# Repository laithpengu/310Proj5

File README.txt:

CMPE 310
Cole Cavanagh & Ethan Swain
Assignment 5: KICAD

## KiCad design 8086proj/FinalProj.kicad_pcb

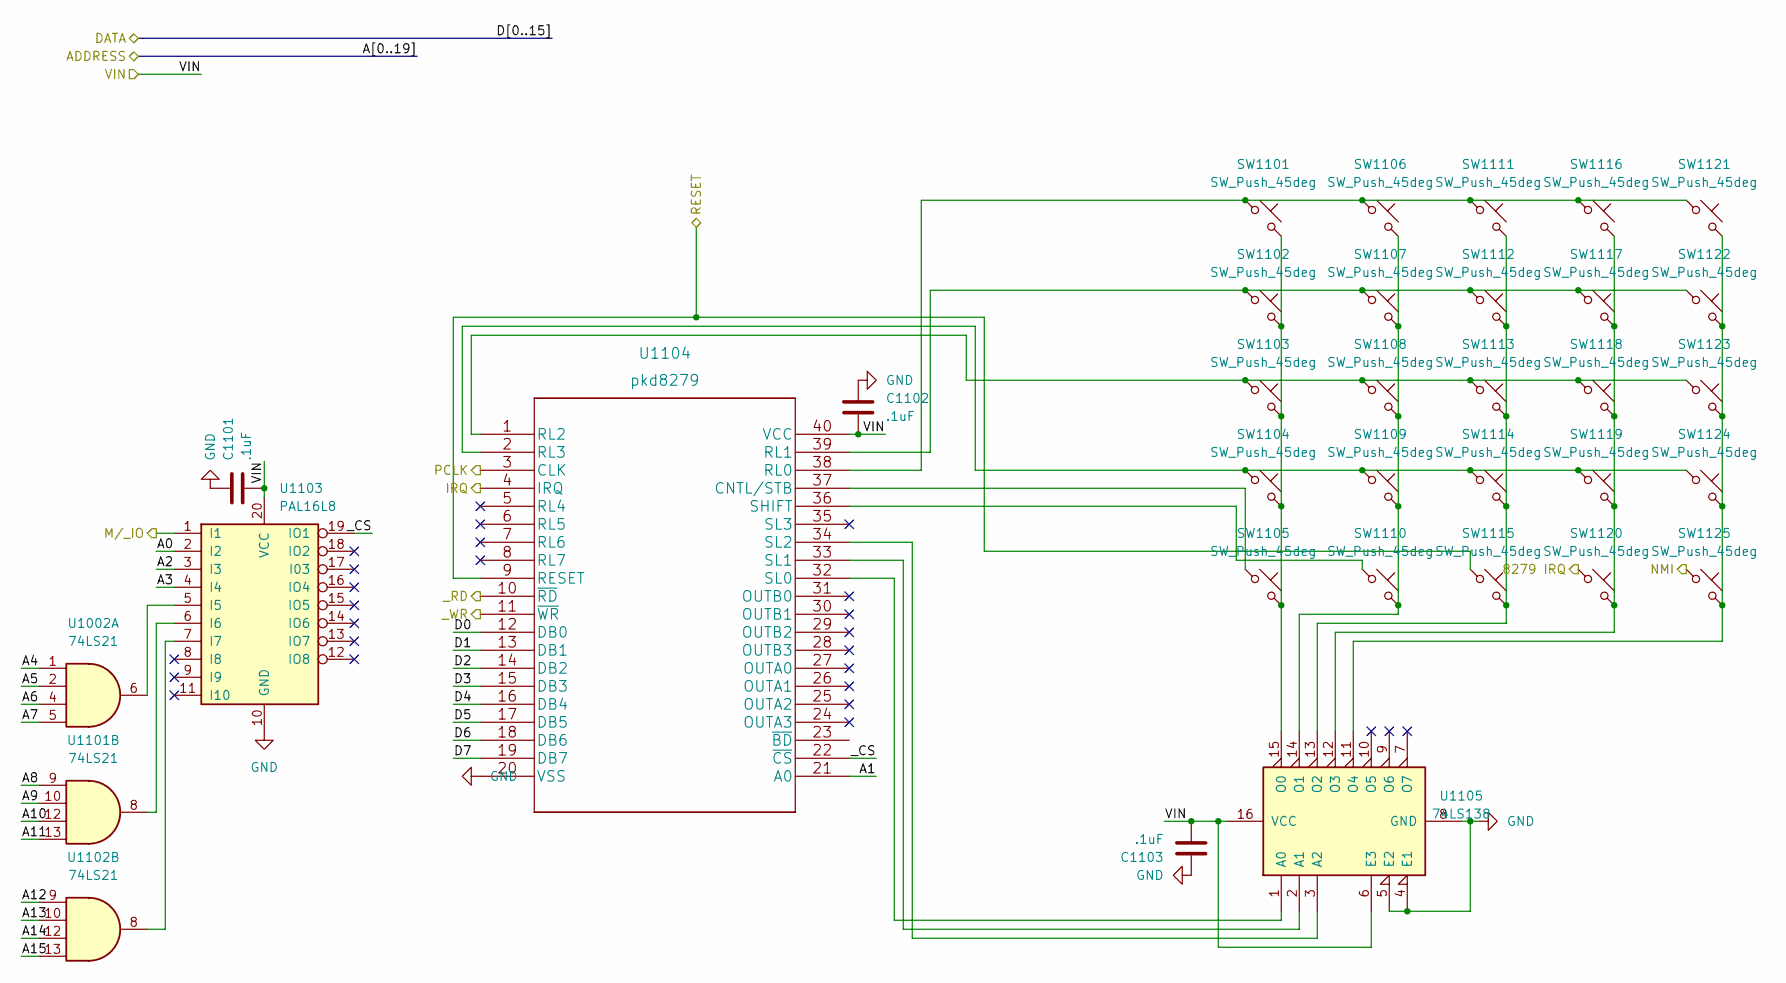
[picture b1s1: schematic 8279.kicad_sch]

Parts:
C1101, C1102, C1103: .1uF; CP_Elec_3x5.3
SW1101, SW1102, SW1103, SW1104, SW1105, SW1106, SW1107, SW1108, SW1109, SW1110, SW1111, SW1112, SW1113, SW1114, SW1115, SW1116, SW1117, SW1118, SW1119, SW1120, SW1121, SW1122, SW1123, SW1124, SW1125: SW_Push_45deg; SW_Cherry_MX_1.00u_Plate
U1002, U1101, U1102: 74LS21; DIP-14_W10.16mm
U1103: PAL16L8; DIP-20_W7.62mm
U1104: pkd8279; DIP-40_W25.4mm
U1105: 74LS138; DIP-16_W7.62mm

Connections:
/8086/INTR: U1104.4 (IRQ); also elsewhere on the board
/8086/NMI: SW1125.1; also elsewhere on the board
/8254/C2out: U1104.3 (CLK); also elsewhere on the board
/8259/8279 IRQ: SW1120.1; also elsewhere on the board
/8279/_CS: U1103.19 (IO1), U1104.22 (~CS)
/16550/A0: U1103.2 (I2); also elsewhere on the board
/16550/A1: U1104.21 (A0); also elsewhere on the board
/16550/A2: U1103.3 (I3); also elsewhere on the board
/16550/A3: U1103.4 (I4); also elsewhere on the board
/16550/A4: U1002.1; also elsewhere on the board
/16550/A5: U1002.2; also elsewhere on the board
/16550/A6: U1002.4; also elsewhere on the board
/16550/A7: U1002.5; also elsewhere on the board
/16550/A8: U1101.9; also elsewhere on the board
/16550/A9: U1101.10; also elsewhere on the board
/16550/A10: U1101.12; also elsewhere on the board
/16550/A11: U1101.13; also elsewhere on the board
/16550/A12: U1102.9; also elsewhere on the board
/16550/A13: U1102.10; also elsewhere on the board
/16550/A14: U1102.12; also elsewhere on the board
/16550/A15: U1102.13; also elsewhere on the board
/16550/D0: U1104.12 (DB0); also elsewhere on the board
/16550/D1: U1104.13 (DB1); also elsewhere on the board
/16550/D2: U1104.14 (DB2); also elsewhere on the board
/16550/D3: U1104.15 (DB3); also elsewhere on the board
/16550/D4: U1104.16 (DB4); also elsewhere on the board
/16550/D5: U1104.17 (DB5); also elsewhere on the board
/16550/D6: U1104.18 (DB6); also elsewhere on the board
/16550/D7: U1104.19 (DB7); also elsewhere on the board
/16550/MR: SW1115.1, U1104.9 (RESET); also elsewhere on the board
/16550/_RD: U1104.10 (~RD); also elsewhere on the board
/16550/_WR: U1104.11 (~WR); also elsewhere on the board
unnamed: SW1101.1, SW1106.1, SW1111.1, SW1116.1, SW1121.1, U1104.38 (RL0)
unnamed: SW1101.2, SW1102.2, SW1103.2, SW1104.2, SW1105.2, U1105.15 (O0)
unnamed: SW1102.1, SW1107.1, SW1112.1, SW1117.1, SW1122.1, U1104.39 (RL1)
unnamed: SW1103.1, SW1108.1, SW1113.1, SW1118.1, SW1123.1, U1104.1 (RL2)
unnamed: SW1104.1, SW1109.1, SW1114.1, SW1119.1, SW1124.1, U1104.2 (RL3)
unnamed: SW1105.1, U1104.37 (CNTL/STB)
unnamed: SW1106.2, SW1107.2, SW1108.2, SW1109.2, SW1110.2, U1105.14 (O1)
unnamed: SW1110.1, U1104.36 (SHIFT)
unnamed: SW1111.2, SW1112.2, SW1113.2, SW1114.2, SW1115.2, U1105.13 (O2)
unnamed: SW1116.2, SW1117.2, SW1118.2, SW1119.2, SW1120.2, U1105.12 (O3)
unnamed: SW1121.2, SW1122.2, SW1123.2, SW1124.2, SW1125.2, U1105.11 (O4)
unnamed: U1002.6, U1103.5 (I5)
unnamed: U1101.8, U1103.6 (I6)
unnamed: U1102.8, U1103.7 (I7)
unnamed: U1104.32 (SL0), U1105.1 (A0)
unnamed: U1104.33 (SL1), U1105.2 (A1)
unnamed: U1104.34 (SL2), U1105.3 (A2)

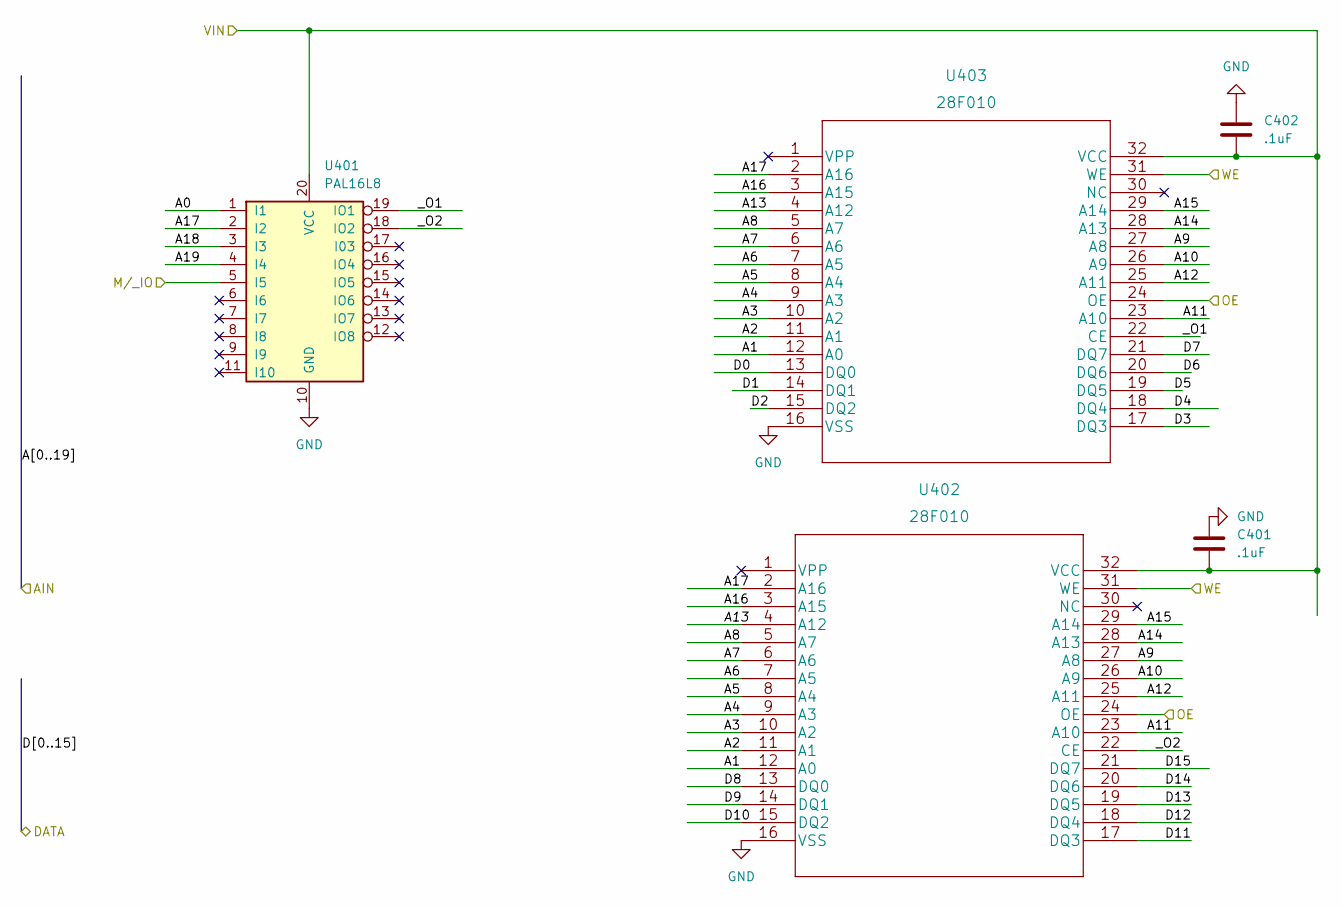
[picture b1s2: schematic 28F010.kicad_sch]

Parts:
C401, C402: .1uF; CP_Elec_3x5.3
U401: PAL16L8; DIP-20_W7.62mm
U402, U403: 28F010; DIP-32_W15.24mm

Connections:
/28F010/A16: U402.3 (A15), U403.3 (A15)
/28F010/A17: U401.2 (I2), U402.2 (A16), U403.2 (A16)
/28F010/A18: U401.3 (I3)
/28F010/A19: U401.4 (I4)
/28F010/_O1: U401.19 (IO1), U403.22 (CE)
/28F010/_O2: U401.18 (IO2), U402.22 (CE)
/16550/A0: U401.1 (I1); also elsewhere on the board
/16550/A1: U402.12 (A0), U403.12 (A0); also elsewhere on the board
/16550/A2: U402.11 (A1), U403.11 (A1); also elsewhere on the board
/16550/A3: U402.10 (A2), U403.10 (A2); also elsewhere on the board
/16550/A4: U402.9 (A3), U403.9 (A3); also elsewhere on the board
/16550/A5: U402.8 (A4), U403.8 (A4); also elsewhere on the board
/16550/A6: U402.7 (A5), U403.7 (A5); also elsewhere on the board
/16550/A7: U402.6 (A6), U403.6 (A6); also elsewhere on the board
/16550/A8: U402.5 (A7), U403.5 (A7); also elsewhere on the board
/16550/A9: U402.27 (A8), U403.27 (A8); also elsewhere on the board
/16550/A10: U402.26 (A9), U403.26 (A9); also elsewhere on the board
/16550/A11: U402.23 (A10), U403.23 (A10); also elsewhere on the board
/16550/A12: U402.25 (A11), U403.25 (A11); also elsewhere on the board
/16550/A13: U402.4 (A12), U403.4 (A12); also elsewhere on the board
/16550/A14: U402.28 (A13), U403.28 (A13); also elsewhere on the board
/16550/A15: U402.29 (A14), U403.29 (A14); also elsewhere on the board
/16550/D0: U403.13 (DQ0); also elsewhere on the board
/16550/D1: U403.14 (DQ1); also elsewhere on the board
/16550/D2: U403.15 (DQ2); also elsewhere on the board
/16550/D3: U403.17 (DQ3); also elsewhere on the board
/16550/D4: U403.18 (DQ4); also elsewhere on the board
/16550/D5: U403.19 (DQ5); also elsewhere on the board
/16550/D6: U403.20 (DQ6); also elsewhere on the board
/16550/D7: U403.21 (DQ7); also elsewhere on the board
/16550/D8: U402.13 (DQ0); also elsewhere on the board
/16550/D9: U402.14 (DQ1); also elsewhere on the board
/16550/D10: U402.15 (DQ2); also elsewhere on the board
/16550/D11: U402.17 (DQ3); also elsewhere on the board
/16550/D12: U402.18 (DQ4); also elsewhere on the board
/16550/D13: U402.19 (DQ5); also elsewhere on the board
/16550/D14: U402.20 (DQ6); also elsewhere on the board
/16550/D15: U402.21 (DQ7); also elsewhere on the board
/16550/M/_IO: U401.5 (I5); also elsewhere on the board
/16550/_RD: U402.24 (OE), U403.24 (OE); also elsewhere on the board
/16550/_WR: U402.31 (WE), U403.31 (WE); also elsewhere on the board

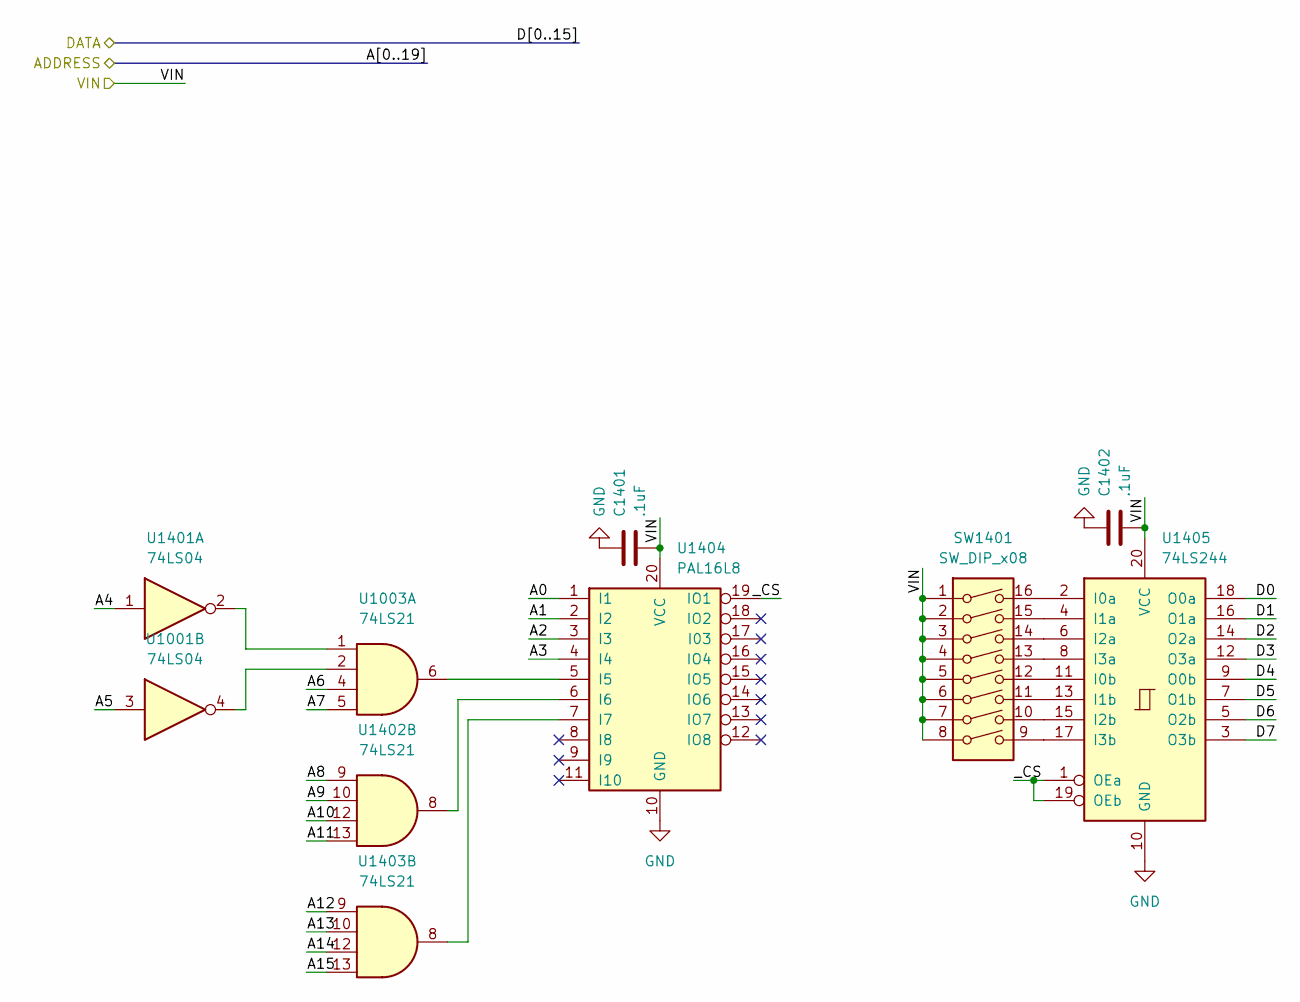
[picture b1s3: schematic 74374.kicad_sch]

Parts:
C1401, C1402: .1uF; CP_Elec_3x5.3
SW1401: SW_DIP_x08; SW_DIP_SPSTx08_Slide_6.7x21.88mm_W6.73mm_P2.54mm_LowProfile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
U1001, U1401: 74LS04; DIP-14_W10.16mm
U1003, U1402, U1403: 74LS21; DIP-14_W10.16mm
U1404: PAL16L8; DIP-20_W7.62mm
U1405: 74LS244; DIP-20_W7.62mm

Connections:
/16550/A0: U1404.1 (I1); also elsewhere on the board
/16550/A1: U1404.2 (I2); also elsewhere on the board
/16550/A2: U1404.3 (I3); also elsewhere on the board
/16550/A3: U1404.4 (I4); also elsewhere on the board
/16550/A4: U1401.1; also elsewhere on the board
/16550/A5: U1001.3; also elsewhere on the board
/16550/A6: U1003.4; also elsewhere on the board
/16550/A7: U1003.5; also elsewhere on the board
/16550/A8: U1402.9; also elsewhere on the board
/16550/A9: U1402.10; also elsewhere on the board
/16550/A10: U1402.12; also elsewhere on the board
/16550/A11: U1402.13; also elsewhere on the board
/16550/A12: U1403.9; also elsewhere on the board
/16550/A13: U1403.10; also elsewhere on the board
/16550/A14: U1403.12; also elsewhere on the board
/16550/A15: U1403.13; also elsewhere on the board
/16550/D0: U1405.18 (O0a); also elsewhere on the board
/16550/D1: U1405.16 (O1a); also elsewhere on the board
/16550/D2: U1405.14 (O2a); also elsewhere on the board
/16550/D3: U1405.12 (O3a); also elsewhere on the board
/16550/D4: U1405.9 (O0b); also elsewhere on the board
/16550/D5: U1405.7 (O1b); also elsewhere on the board
/16550/D6: U1405.5 (O2b); also elsewhere on the board
/16550/D7: U1405.3 (O3b); also elsewhere on the board
/74374/_CS: U1404.19 (IO1), U1405.1 (OEa), U1405.19 (OEb)
unnamed: SW1401.9, U1405.17 (I3b)
unnamed: SW1401.10, U1405.15 (I2b)
unnamed: SW1401.11, U1405.13 (I1b)
unnamed: SW1401.12, U1405.11 (I0b)
unnamed: SW1401.13, U1405.8 (I3a)
unnamed: SW1401.14, U1405.6 (I2a)
unnamed: SW1401.15, U1405.4 (I1a)
unnamed: SW1401.16, U1405.2 (I0a)
unnamed: U1001.4, U1003.2
unnamed: U1003.1, U1401.2
unnamed: U1003.6, U1404.5 (I5)
unnamed: U1402.8, U1404.6 (I6)
unnamed: U1403.8, U1404.7 (I7)

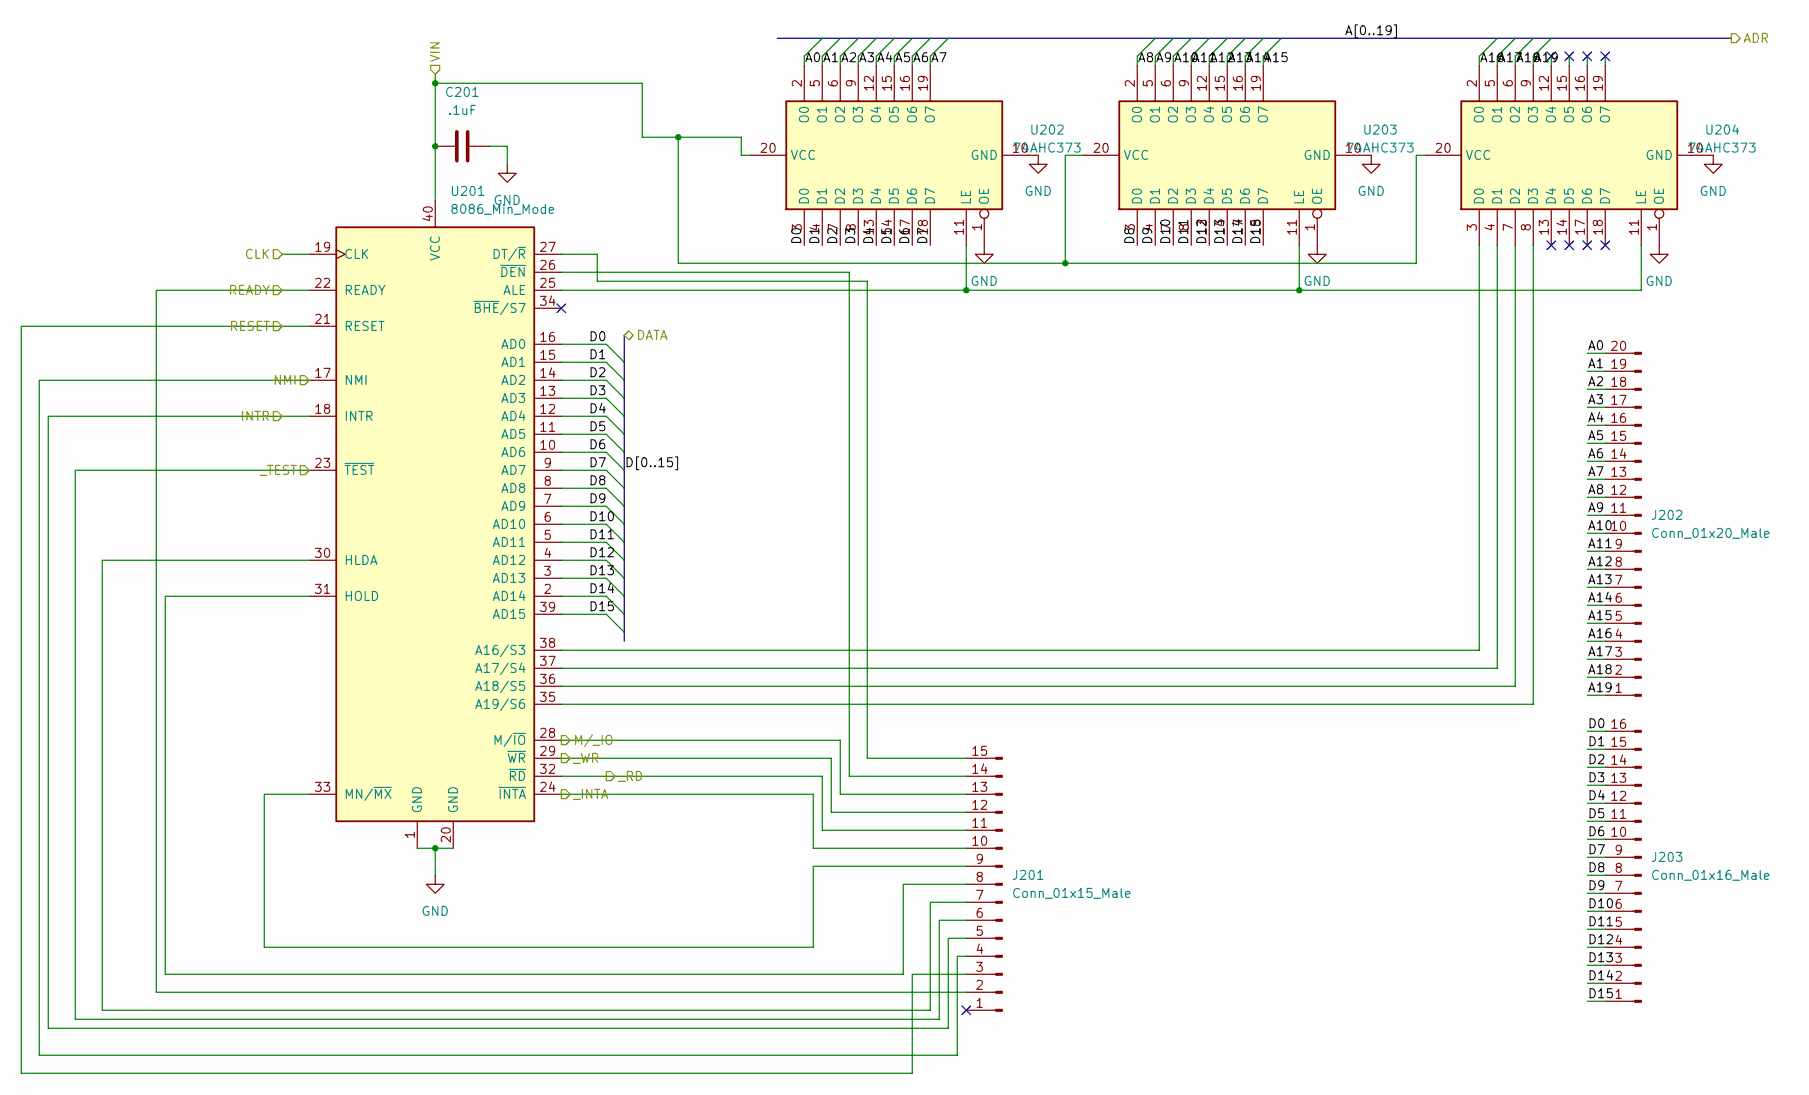
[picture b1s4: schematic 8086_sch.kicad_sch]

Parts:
C201: .1uF; CP_Elec_3x5.3
J201: Conn_01x15_Male; PinHeader_1x15_P1.00mm_Vertical
J202: Conn_01x20_Male; PinHeader_1x20_P1.00mm_Vertical
J203: Conn_01x16_Male; PinHeader_1x16_P1.00mm_Vertical
U201: 8086_Min_Mode; DIP-40_W15.24mm
U202, U203, U204: 74AHC373; DIP-20_W7.62mm

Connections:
/8086/A16: J202.4, U204.2 (O0)
/8086/A17: J202.3, U204.5 (O1)
/8086/A18: J202.2, U204.6 (O2)
/8086/A19: J202.1, U204.9 (O3)
/8086/CLK: U201.19 (CLK); also elsewhere on the board
/8086/INTR: J201.5, U201.18 (INTR); also elsewhere on the board
/8086/NMI: J201.4, U201.17 (NMI); also elsewhere on the board
/8086/READY: J201.2, U201.22 (READY); also elsewhere on the board
/8086/_TEST: J201.6, U201.23 (~TEST)
/16550/A0: J202.20, U202.2 (O0); also elsewhere on the board
/16550/A1: J202.19, U202.5 (O1); also elsewhere on the board
/16550/A2: J202.18, U202.6 (O2); also elsewhere on the board
/16550/A3: J202.17, U202.9 (O3); also elsewhere on the board
/16550/A4: J202.16, U202.12 (O4); also elsewhere on the board
/16550/A5: J202.15, U202.15 (O5); also elsewhere on the board
/16550/A6: J202.14, U202.16 (O6); also elsewhere on the board
/16550/A7: J202.13, U202.19 (O7); also elsewhere on the board
/16550/A8: J202.12, U203.2 (O0); also elsewhere on the board
/16550/A9: J202.11, U203.5 (O1); also elsewhere on the board
/16550/A10: J202.10, U203.6 (O2); also elsewhere on the board
/16550/A11: J202.9, U203.9 (O3); also elsewhere on the board
/16550/A12: J202.8, U203.12 (O4); also elsewhere on the board
/16550/A13: J202.7, U203.15 (O5); also elsewhere on the board
/16550/A14: J202.6, U203.16 (O6); also elsewhere on the board
/16550/A15: J202.5, U203.19 (O7); also elsewhere on the board
/16550/D0: J203.16, U201.16 (AD0), U202.3 (D0); also elsewhere on the board
/16550/D1: J203.15, U201.15 (AD1), U202.4 (D1); also elsewhere on the board
/16550/D2: J203.14, U201.14 (AD2), U202.7 (D2); also elsewhere on the board
/16550/D3: J203.13, U201.13 (AD3), U202.8 (D3); also elsewhere on the board
/16550/D4: J203.12, U201.12 (AD4), U202.13 (D4); also elsewhere on the board
/16550/D5: J203.11, U201.11 (AD5), U202.14 (D5); also elsewhere on the board
/16550/D6: J203.10, U201.10 (AD6), U202.17 (D6); also elsewhere on the board
/16550/D7: J203.9, U201.9 (AD7), U202.18 (D7); also elsewhere on the board
/16550/D8: J203.8, U201.8 (AD8), U203.3 (D0); also elsewhere on the board
/16550/D9: J203.7, U201.7 (AD9), U203.4 (D1); also elsewhere on the board
/16550/D10: J203.6, U201.6 (AD10), U203.7 (D2); also elsewhere on the board
/16550/D11: J203.5, U201.5 (AD11), U203.8 (D3); also elsewhere on the board
/16550/D12: J203.4, U201.4 (AD12), U203.13 (D4); also elsewhere on the board
/16550/D13: J203.3, U201.3 (AD13), U203.14 (D5); also elsewhere on the board
/16550/D14: J203.2, U201.2 (AD14), U203.17 (D6); also elsewhere on the board
/16550/D15: J203.1, U201.39 (AD15), U203.18 (D7); also elsewhere on the board
/16550/MR: J201.3, U201.21 (RESET); also elsewhere on the board
/16550/M/_IO: J201.13, U201.28 (M/~IO); also elsewhere on the board
/16550/_RD: J201.11, U201.32 (~RD); also elsewhere on the board
/16550/_WR: J201.12, U201.29 (~WR); also elsewhere on the board
unnamed: J201.7, U201.30 (HLDA)
unnamed: J201.8, U201.31 (HOLD)
unnamed: J201.9, U201.33 (MN/~MX)
unnamed: J201.14, U201.26 (~DEN)
unnamed: J201.15, U201.27 (DT/~R)
unnamed: U201.25 (ALE), U202.11 (LE), U203.11 (LE), U204.11 (LE)
unnamed: U201.35 (A19/S6), U204.8 (D3)
unnamed: U201.36 (A18/S5), U204.7 (D2)
unnamed: U201.37 (A17/S4), U204.4 (D1)
unnamed: U201.38 (A16/S3), U204.3 (D0)

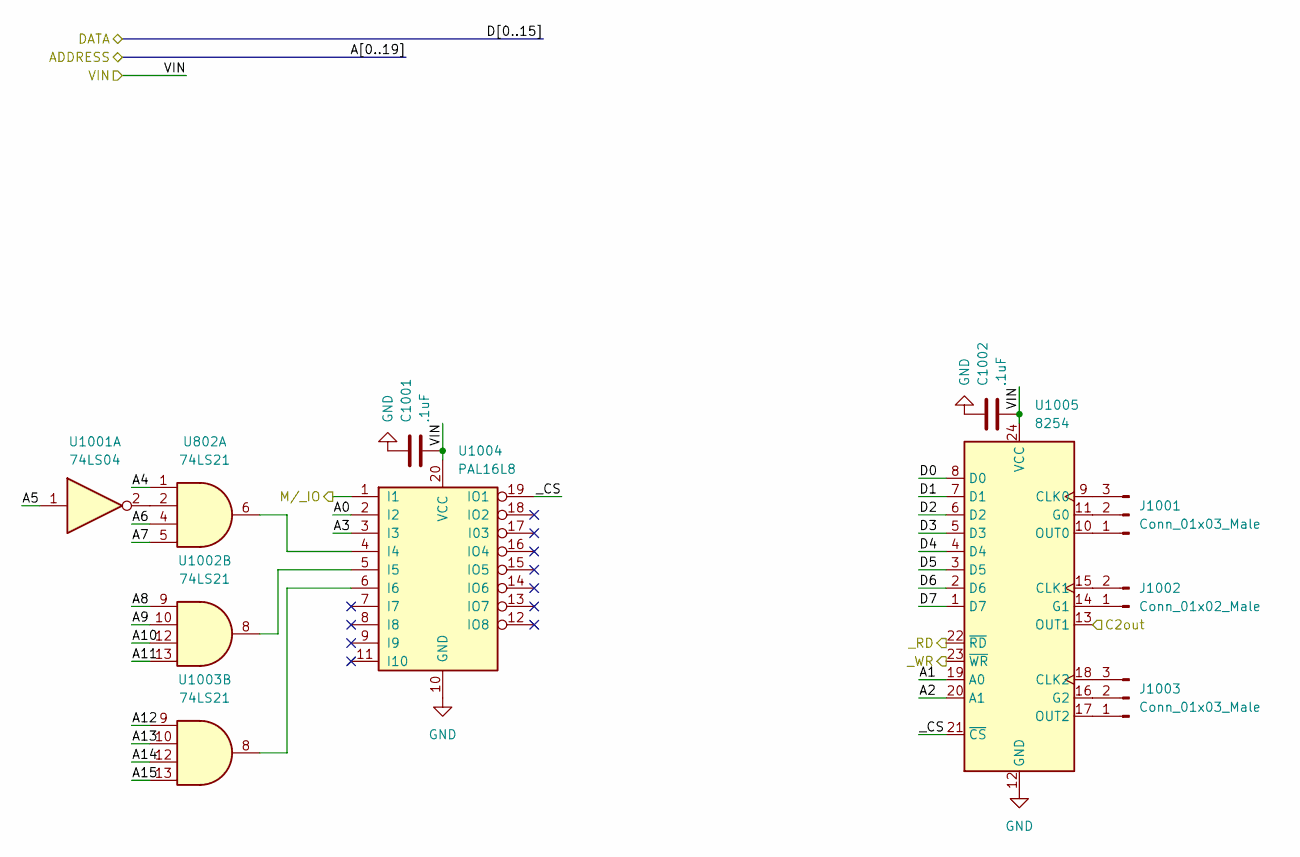
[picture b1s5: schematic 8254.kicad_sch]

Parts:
C1001, C1002: .1uF; CP_Elec_3x5.3
J1001, J1003: Conn_01x03_Male; PinHeader_1x03_P1.00mm_Vertical
J1002: Conn_01x02_Male; PinHeader_1x02_P1.00mm_Vertical
U802, U1002, U1003: 74LS21; DIP-14_W10.16mm
U1001: 74LS04; DIP-14_W10.16mm
U1004: PAL16L8; DIP-20_W7.62mm
U1005: 8254; DIP-24_W15.24mm

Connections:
/8254/C2out: U1005.13 (OUT1); also elsewhere on the board
/8254/_CS: U1004.19 (IO1), U1005.21 (~CS)
/16550/A0: U1004.2 (I2); also elsewhere on the board
/16550/A1: U1005.19 (A0); also elsewhere on the board
/16550/A2: U1005.20 (A1); also elsewhere on the board
/16550/A3: U1004.3 (I3); also elsewhere on the board
/16550/A4: U802.1; also elsewhere on the board
/16550/A5: U1001.1; also elsewhere on the board
/16550/A6: U802.4; also elsewhere on the board
/16550/A7: U802.5; also elsewhere on the board
/16550/A8: U1002.9; also elsewhere on the board
/16550/A9: U1002.10; also elsewhere on the board
/16550/A10: U1002.12; also elsewhere on the board
/16550/A11: U1002.13; also elsewhere on the board
/16550/A12: U1003.9; also elsewhere on the board
/16550/A13: U1003.10; also elsewhere on the board
/16550/A14: U1003.12; also elsewhere on the board
/16550/A15: U1003.13; also elsewhere on the board
/16550/D0: U1005.8 (D0); also elsewhere on the board
/16550/D1: U1005.7 (D1); also elsewhere on the board
/16550/D2: U1005.6 (D2); also elsewhere on the board
/16550/D3: U1005.5 (D3); also elsewhere on the board
/16550/D4: U1005.4 (D4); also elsewhere on the board
/16550/D5: U1005.3 (D5); also elsewhere on the board
/16550/D6: U1005.2 (D6); also elsewhere on the board
/16550/D7: U1005.1 (D7); also elsewhere on the board
/16550/M/_IO: U1004.1 (I1); also elsewhere on the board
/16550/_RD: U1005.22 (~RD); also elsewhere on the board
/16550/_WR: U1005.23 (~WR); also elsewhere on the board
unnamed: J1001.1, U1005.10 (OUT0)
unnamed: J1001.2, U1005.11 (G0)
unnamed: J1001.3, U1005.9 (CLK0)
unnamed: J1002.1, U1005.14 (G1)
unnamed: J1002.2, U1005.15 (CLK1)
unnamed: J1003.1, U1005.17 (OUT2)
unnamed: J1003.2, U1005.16 (G2)
unnamed: J1003.3, U1005.18 (CLK2)
unnamed: U802.2, U1001.2
unnamed: U1002.8, U1004.5 (I5)
unnamed: U1003.8, U1004.6 (I6)
unnamed: U802.6, U1004.4 (I4)

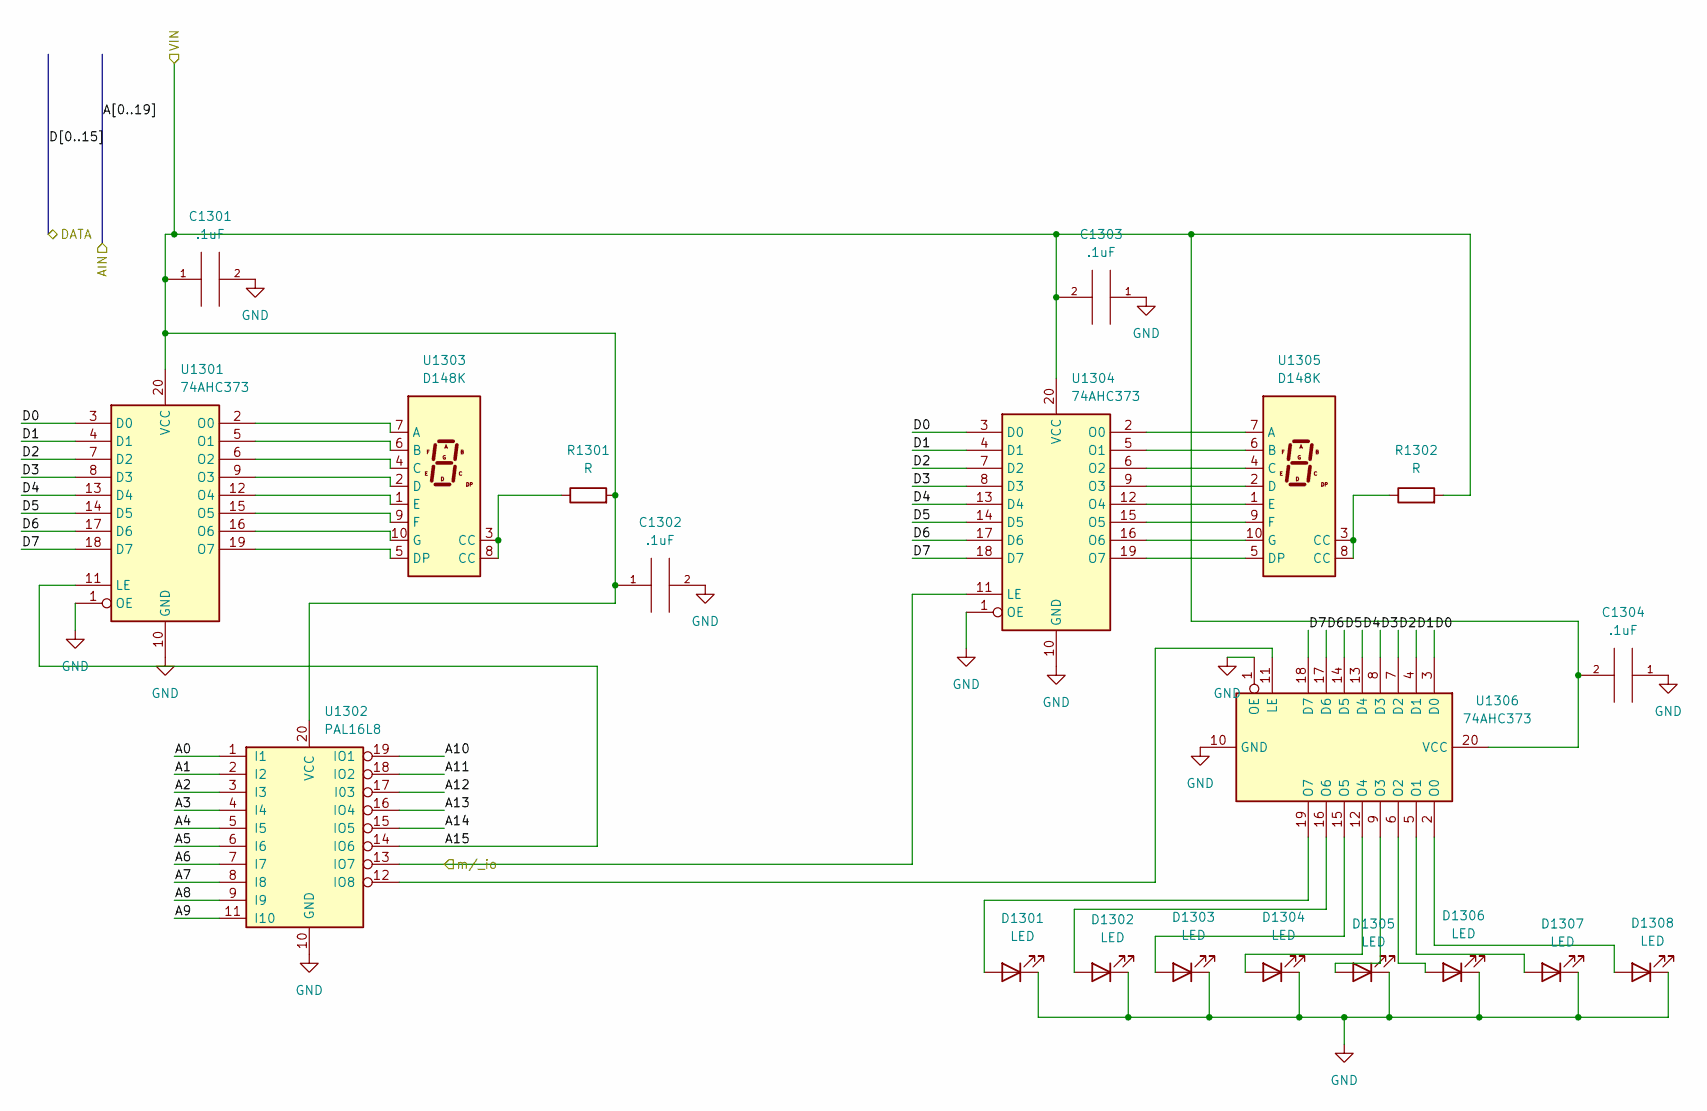
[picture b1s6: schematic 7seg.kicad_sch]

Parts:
C1301, C1302, C1303, C1304: .1uF; CP_Elec_3x5.3
D1301, D1302, D1303, D1304, D1305, D1306, D1307, D1308: LED; LED_0201_0603Metric
R1301, R1302: R; R_0201_0603Metric
U1301, U1304, U1306: 74AHC373; DIP-20_W7.62mm
U1302: PAL16L8; DIP-20_W7.62mm
U1303, U1305: D148K; D1X8K

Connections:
/16550/A0: U1302.1 (I1); also elsewhere on the board
/16550/A1: U1302.2 (I2); also elsewhere on the board
/16550/A2: U1302.3 (I3); also elsewhere on the board
/16550/A3: U1302.4 (I4); also elsewhere on the board
/16550/A4: U1302.5 (I5); also elsewhere on the board
/16550/A5: U1302.6 (I6); also elsewhere on the board
/16550/A6: U1302.7 (I7); also elsewhere on the board
/16550/A7: U1302.8 (I8); also elsewhere on the board
/16550/A8: U1302.9 (I9); also elsewhere on the board
/16550/A9: U1302.11 (I10); also elsewhere on the board
/16550/A10: U1302.19 (IO1); also elsewhere on the board
/16550/A11: U1302.18 (IO2); also elsewhere on the board
/16550/A12: U1302.17 (I03); also elsewhere on the board
/16550/A13: U1302.16 (IO4); also elsewhere on the board
/16550/A14: U1302.15 (IO5); also elsewhere on the board
/16550/A15: U1301.11 (LE), U1302.14 (IO6); also elsewhere on the board
/16550/D0: U1301.3 (D0), U1304.3 (D0), U1306.3 (D0); also elsewhere on the board
/16550/D1: U1301.4 (D1), U1304.4 (D1), U1306.4 (D1); also elsewhere on the board
/16550/D2: U1301.7 (D2), U1304.7 (D2), U1306.7 (D2); also elsewhere on the board
/16550/D3: U1301.8 (D3), U1304.8 (D3), U1306.8 (D3); also elsewhere on the board
/16550/D4: U1301.13 (D4), U1304.13 (D4), U1306.13 (D4); also elsewhere on the board
/16550/D5: U1301.14 (D5), U1304.14 (D5), U1306.14 (D5); also elsewhere on the board
/16550/D6: U1301.17 (D6), U1304.17 (D6), U1306.17 (D6); also elsewhere on the board
/16550/D7: U1301.18 (D7), U1304.18 (D7), U1306.18 (D7); also elsewhere on the board
/16550/M/_IO: U1302.13 (IO7), U1304.11 (LE); also elsewhere on the board
unnamed: D1301.2 (A), U1306.19 (O7)
unnamed: D1302.2 (A), U1306.16 (O6)
unnamed: D1303.2 (A), U1306.15 (O5)
unnamed: D1304.2 (A), U1306.12 (O4)
unnamed: D1305.2 (A), U1306.9 (O3)
unnamed: D1306.2 (A), U1306.6 (O2)
unnamed: D1307.2 (A), U1306.5 (O1)
unnamed: D1308.2 (A), U1306.2 (O0)
unnamed: R1301.1, U1303.3 (CC), U1303.8 (CC)
unnamed: R1302.1, U1305.3 (CC), U1305.8 (CC)
unnamed: U1301.2 (O0), U1303.7 (A)
unnamed: U1301.5 (O1), U1303.6 (B)
unnamed: U1301.6 (O2), U1303.4 (C)
unnamed: U1301.9 (O3), U1303.2 (D)
unnamed: U1301.12 (O4), U1303.1 (E)
unnamed: U1301.15 (O5), U1303.9 (F)
unnamed: U1301.16 (O6), U1303.10 (G)
unnamed: U1301.19 (O7), U1303.5 (DP)
unnamed: U1302.12 (IO8), U1306.11 (LE)
unnamed: U1304.2 (O0), U1305.7 (A)
unnamed: U1304.5 (O1), U1305.6 (B)
unnamed: U1304.6 (O2), U1305.4 (C)
unnamed: U1304.9 (O3), U1305.2 (D)
unnamed: U1304.12 (O4), U1305.1 (E)
unnamed: U1304.15 (O5), U1305.9 (F)
unnamed: U1304.16 (O6), U1305.10 (G)
unnamed: U1304.19 (O7), U1305.5 (DP)

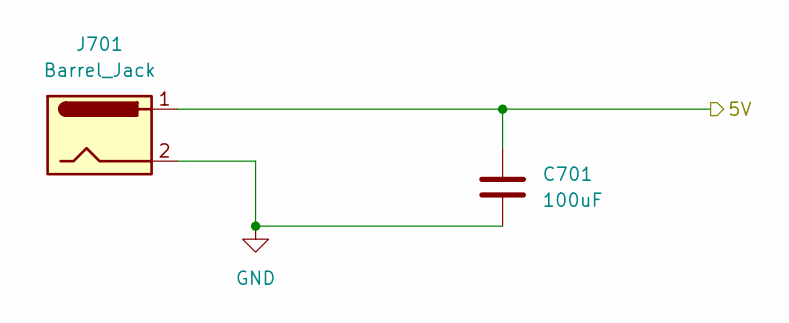
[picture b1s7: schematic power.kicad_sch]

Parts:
C701: 100uF; CP_Elec_3x5.3
J701: Barrel_Jack; BarrelJack_CUI_PJ-063AH_Horizontal

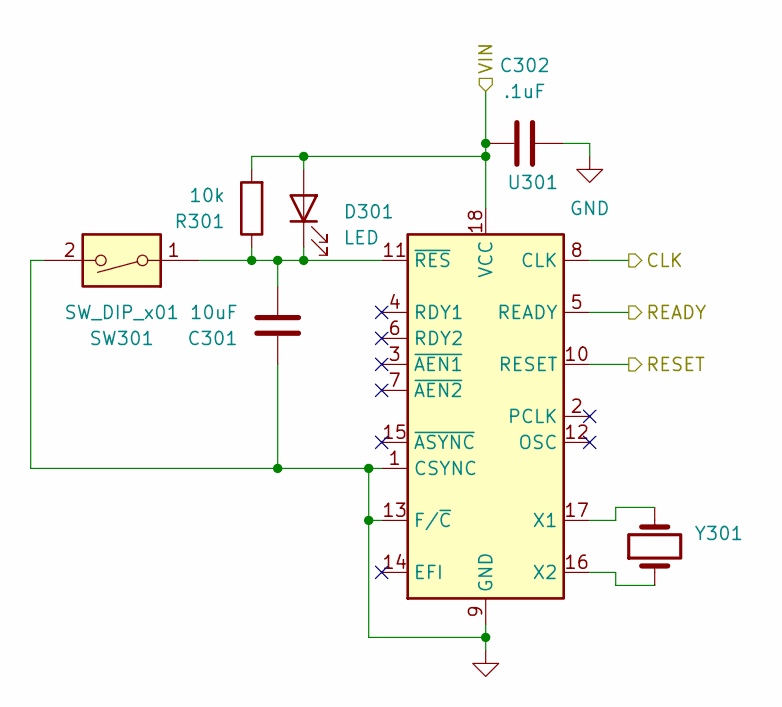
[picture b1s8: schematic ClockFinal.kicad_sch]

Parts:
C301: 10uF; CP_Elec_3x5.3
C302: .1uF; CP_Elec_3x5.3
D301: LED; LED_0201_0603Metric
R301: 10k; R_0201_0603Metric
SW301: SW_DIP_x01; SW_DIP_SPSTx01_Slide_6.7x4.1mm_W6.73mm_P2.54mm_LowProfile_J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
U301: DIP-18_W7.62mm
Y301: Crystal_AT310_D3.0mm_L10.0mm_Horizontal

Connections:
/8086/CLK: U301.8 (CLK); also elsewhere on the board
/8086/READY: U301.5 (READY); also elsewhere on the board
/16550/MR: U301.10 (RESET); also elsewhere on the board
unnamed: C301.2, D301.1 (K), R301.1, SW301.1, U301.11 (~RES)
unnamed: U301.16 (X2), Y301.1
unnamed: U301.17 (X1), Y301.2

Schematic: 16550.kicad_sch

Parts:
C901: .1uF; CP_Elec_3x5.3
J901: DSUB-9; DSUB-9_Female_Horizontal_P2.77x2.84mm_EdgePinOffset7.70mm_H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
R901: 1kohm; R_0201_0603Metric
U901: PAL16L8; DIP-20_W7.62mm
U902: 16550; DIP-40_W15.24mm
U903: max235cpg; DIP-24_W10.16mm
Y901: Crystal_AT310_D3.0mm_L10.0mm_Horizontal

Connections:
/16550/A0: U901.1 (I1); also elsewhere on the board
/16550/A1: U902.28 (A0); also elsewhere on the board
/16550/A2: U902.27 (A1); also elsewhere on the board
/16550/A3: U902.26 (A2); also elsewhere on the board
/16550/A4: U901.2 (I2); also elsewhere on the board
/16550/A5: U901.3 (I3); also elsewhere on the board
/16550/A6: U901.4 (I4); also elsewhere on the board
/16550/A7: U901.5 (I5); also elsewhere on the board
/16550/A8: U901.6 (I6); also elsewhere on the board
/16550/A9: U901.7 (I7); also elsewhere on the board
/16550/A10: U901.8 (I8); also elsewhere on the board
/16550/A11: U901.9 (I9); also elsewhere on the board
/16550/A12: U901.11 (I10); also elsewhere on the board
/16550/A13: U901.19 (IO1); also elsewhere on the board
/16550/A14: U901.18 (IO2); also elsewhere on the board
/16550/A15: U901.17 (I03); also elsewhere on the board
/16550/D8: U902.1 (D0); also elsewhere on the board
/16550/D9: U902.2 (D1); also elsewhere on the board
/16550/D10: U902.3 (D2); also elsewhere on the board
/16550/D11: U902.4 (D3); also elsewhere on the board
/16550/D12: U902.5 (D4); also elsewhere on the board
/16550/D13: U902.6 (D5); also elsewhere on the board
/16550/D14: U902.7 (D6); also elsewhere on the board
/16550/D15: U902.8 (D7); also elsewhere on the board
/16550/INTR: U902.30 (INTR); also elsewhere on the board
/16550/MR: U902.35 (MR); also elsewhere on the board
/16550/M/_IO: U901.16 (IO4); also elsewhere on the board
/16550/_RD: U902.21 (~RD); also elsewhere on the board
/16550/_WR: U902.18 (~WR); also elsewhere on the board
unnamed: J901.1 (DCD), J901.4 (DTR), J901.6 (DSR), U903.23 (R3OUT)
unnamed: J901.2 (RDX), U903.4 (T2OUT)
unnamed: J901.9 (RI), U903.2 (T3OUT)
unnamed: R901.2, U902.12 (CS0), U902.13 (CS1)
unnamed: U901.15 (IO5), U902.14 (~CS2)
unnamed: U902.10 (SIN), U903.6 (R2OUT)
unnamed: U902.11 (SOUT), U903.7 (T2IN)
unnamed: U902.9 (RCLK), U902.15 (~BAUDOUT)
unnamed: U902.16 (XIN), Y901.1
unnamed: U902.17 (XOUT), Y901.2
unnamed: U902.34 (~OUT1), U903.15 (T3IN)
